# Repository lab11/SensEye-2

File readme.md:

# SensEye-2
**Sight-Guided Search and Depth Detection**

Based on the original SensEye design by Russ Bielawaski:  [repo](https://github.com/downbeat/senseye) 

##System Architecture

See the diagram below for an overview of the hardware and software stack for SensEye-2:

##OpenCV Image Processing
There are currently two python scripts written to implement OpenCV functions on top of images captured from the system. They are located in `software/client/opencv_detection` and also have the ability to measure run-time. Examples are shown below:
### Blob Detection 
Used to find the location of the pupil on the inward facing camera.

	python blob_detect.py
	Runtime of Blob Detection: 0.161993980408 seconds

### Depth Detection
Used to calculate the depth of the image based on the disparity between the two outward facing cameras.

	python disparity.py
	Runtime of Depth Detection: 0.360285043716 seconds

To complete this processing in real-time on the host computer, the run-time would have to be on the order of `0.04 seconds` as the imager captures images at a rate of approximately `25 hertz`.   

## Installation
### A note on operating systems
This installation uses Windows for Libero and Linux for uCLinux compilation. 
Specifically, 64-bit Windows 8 and 64-bit Ubuntu 14.04 LTS. Other options may be
successful

### Libero SoC
1. Download Libero from the following [link](http://www.microsemi.com/products/fpga-soc/design-resources/design-software/libero-soc#downloads).

2. Register for free gold 1-year disk ID locked license, follow instructions in email  

3. Install service pack update (if on Windows 8, you may need to disable driver signatures in order to install the FlashPro driver)

**Note**: Libero can be installed on Linux, but has been found to be problematic

### OpenCV
1. Download and install OpenCV, this [link](http://milq.github.io/install-opencv-ubuntu-debian/) worked well.
2. Ensure OpenCV installed in `/usr/local/include/`

### TFTP Server
1. Download and install a TFTP server, this [link](https://mohammadthalif.wordpress.com/2010/03/05/installing-and-testing-tftpd-in-ubuntudebian/) worked well.

## Setup

### Libero Project
1. Open `senseye.prjx` (you will get errors: "Unable to find..."")

2. Double click TOPLEVEL in the Design Hierarchy area to open it in the main window

3. Double click MSS\_CORE3\_MSS\_0 to open it in a new tab  
    1. Double click the ENVM block
    2. Right click the first client listed and select Modify Client.
    3. Change the location of the memory file to `your_SensEye-2_location\SensEye-2\software\smartfusion\Emcraft_Firmware\u-boot.hex`. 
    4. Click the Generate Component button in the main window (yellow cylinder with gear). 

4. Go to TOPLEVEL tab  
5. Click the Generate Programming Data button in the Design Flow area (green arrow)

Project should build appropriately.

**Note**: Ensure all of the MSS components are updated by clicking the Catalog tab then the `Download them now!` button (Libero should show the message `New cores are available`). Also ensure reset line into imager is inverted (in TOPLEVEL).

### uCLinux Build Environment
Open the Linux Cortex M User Manual available from Emcraft's SmartFusion webpage  
Follow the directions in Section 4.1

The `linux-cortexm-1.12.0/` folder should be extracted to the same location as the git repo  
(To get a new version of the cross-compiler, click [here](http://www.mentor.com/embedded-software/sourcery-tools/sourcery-codebench/editions/lite-edition/arm-uclinux.html), but you should probably stick with the one given by emcraft)  

`.bashrc` will need to be updated to run the following:

    cd <linux install directory>
    . ACTIVATE.sh
    cd -

**Note**: the cross compiler tools work for me on 64-bit fedora, but not in a shared folder. You may need to install ia32-libs or equivalent if you are on a 64-bit system

### TFTP Server
Test that the server is working by running:

    touch <tftpboot directory>/foo
    tftp 127.0.0.1
    get foo
    quit

**Note**: sometimes it is necessary to run this with `sudo`. 

The get request should complete immediately without an issue

Open a serial connection at 115200 baud. An example of this is below (assuming it is `ttyUSB0`)
	
	screen /dev/ttyUSB0 115200  

**Note**: Sometimes it is necessary to run this with `sudo` . Also if there is only a blank screen press `Enter` a few times and if that doesn't work, press `Ctrl-C` to kill the current program and reboot.

Find device IP address, from U-Boot:

    run flashboot
    udhcpc
    ifconfig
    reboot

Modify the environment variables on the SmartFusion board, from U-Boot:

    setenv netmask 255.255.255.0
    setenv gatewayip <device ip address top 24 bits>.1
    setenv ipaddr <device ip address>
    setenv serverip <server ip address>
    setenv image senseye_proj.uImage
    saveenv
    run netboot

### NFS Server
Follow instructions online to install an NFS server and enable it

After the device has booted run
    
    mount -t nfs -o proto=tcp,nolock,port=2049 <server ip address>:/<server nfs folder> /mnt

A script to do this has been included as `nfs.sh`

### Load Stonyman
Navigate to the `SensEye-2/software/uclinux/senseye_proj/` directory and edit `makescript`

	cp senseye_proj.uImage <your tftpboot directory>

Then run
    
    ./makescript

This should redirect all compile messages to the `compile.log` file. Run following commands on device

    ./load_stonyman.sh
    ./senseye_serv

The Stonyman controller software should now be loaded and ready to begin reading in images.

### Setting up client
Ensure OpenCV installed in `/usr/local/include/`

Change address of SmartFusion board in `SensEye-2/software/client/senseye_client/senseye_client.c` to current IP address (found by running `printenv` on the SmartFusion board):

    #define INSIGHT_SERV_ADDR     ("141.212.11.215") 

Navigate to the `SensEye-2/software/client/senseye_client` directory and run. 
  
    ./makescript

This should redirect all compile messages to the file `compile.out`

**Note**: while `senseye_serv` is running on the SmartFusion it waits for a connection from the client which is created by running `senseye_client`, then images should appear on the screen if a Stonyman is connected correctly.

### Hardware Configuration
The hardware can be somewhat tricky to configure correctly. First, build the circuit specified in `hardware/schematics/stonyman_breakout.pdf`. Ensure to tie a resistor (30k) to ground from the analog out (AN) of the Stonyman, and place a capacitor across the power supply rails.

**Calibration:** The configuration of the parameters in `software/uclinux/stonyman/stonyman_2.h` is dependent on whether the system is run at 3.3 Volts or 5 Volts. As of now the system is configured for 3.3 V. This can be changed by modifying the `define` statements based on empirical evidence.

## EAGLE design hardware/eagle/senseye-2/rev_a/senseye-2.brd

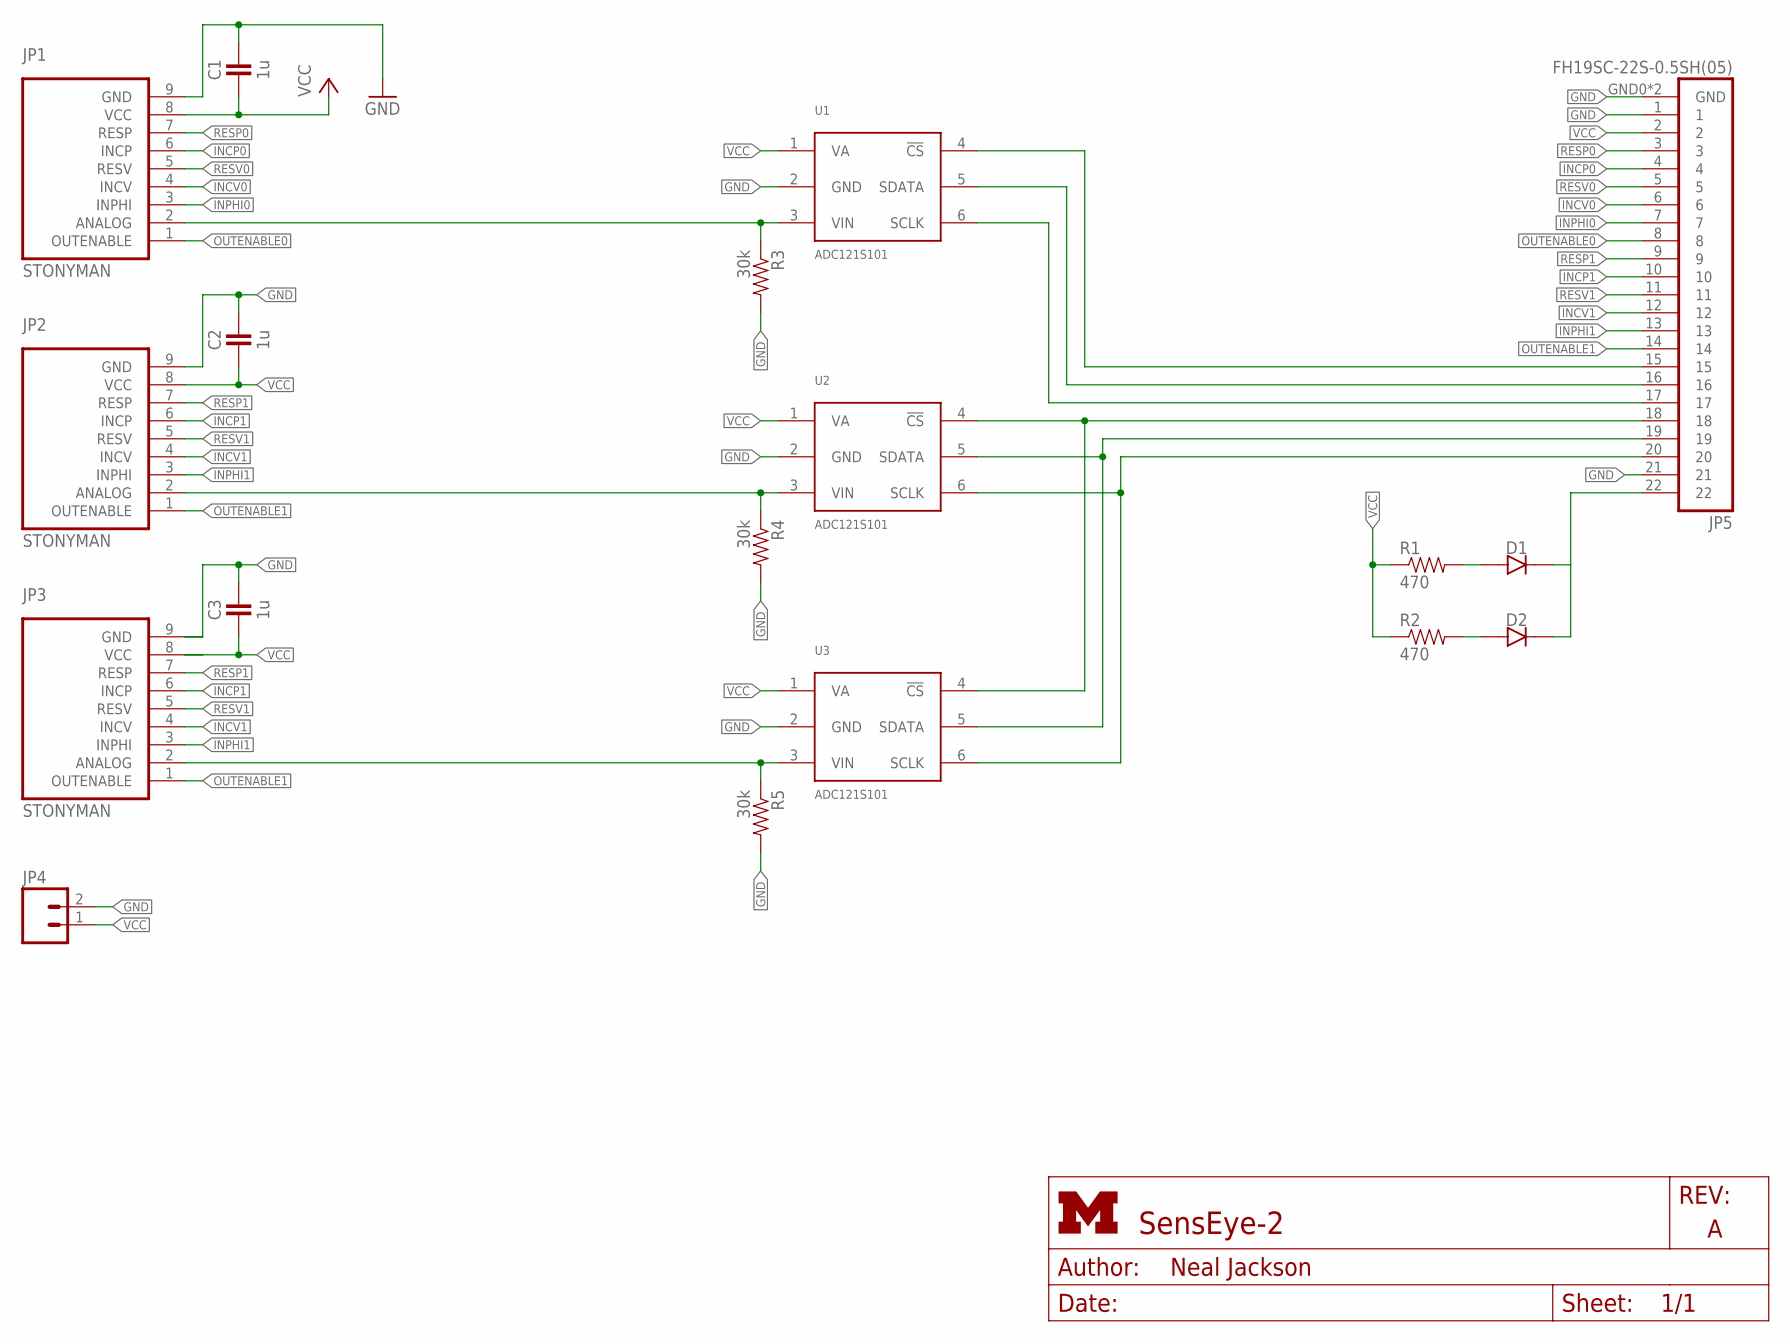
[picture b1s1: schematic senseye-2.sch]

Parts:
C1, C2, C3: 1u; 0402_CAP
D1, D2: DIODE0603; 0603-DIODE
JP1, JP2, JP3: STONYMAN; 1X09
JP4: M02PTH; 1X02
JP5: FH19SC-22S-0.5SH(05)
R1, R2: 470; 0402_RES
R3, R4, R5: 30k; 0402_RES
U1, U2, U3: ADC121S101; SOT-23-6

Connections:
!CS0: JP5.15, U1.4 (!CS)
ANALOG0: JP1.2 (ANALOG), R3.1, U1.3 (VIN)
GND: C1.1, C2.1, C3.1, JP1.9 (GND), JP2.9 (GND), JP3.9 (GND), JP4.2, JP5.1, JP5.21, JP5.GND0 (GND), JP5.GND1 (GND), R3.2, R4.2, R5.2, U1.2 (GND), U2.2 (GND), U3.2 (GND)
INCP0: JP1.6 (INCP), JP5.4
INCP1: JP2.6 (INCP), JP3.6 (INCP), JP5.10
INCV0: JP1.4 (INCV), JP5.6
INCV1: JP2.4 (INCV), JP3.4 (INCV), JP5.12
INPHI0: JP1.3 (INPHI), JP5.7
INPHI1: JP2.3 (INPHI), JP3.3 (INPHI), JP5.13
LED: D1.2 (CATHODE), D2.2 (CATHODE), JP5.22
unnamed: JP2.2 (ANALOG), R4.1, U2.3 (VIN)
unnamed: D1.1 (ANODE), R1.2
unnamed: JP3.2 (ANALOG), R5.1, U3.3 (VIN)
unnamed: D2.1 (ANODE), R2.2
unnamed: JP5.18, U2.4 (!CS), U3.4 (!CS)
OUTENABLE0: JP1.1 (OUTENABLE), JP5.8
OUTENABLE1: JP2.1 (OUTENABLE), JP3.1 (OUTENABLE), JP5.14
RESP0: JP1.7 (RESP), JP5.3
RESP1: JP2.7 (RESP), JP3.7 (RESP), JP5.9
RESV0: JP1.5 (RESV), JP5.5
RESV1: JP2.5 (RESV), JP3.5 (RESV), JP5.11
SCLK0: JP5.17, U1.6 (SCLK)
SCLK1: JP5.20, U2.6 (SCLK), U3.6 (SCLK)
SDATA0: JP5.16, U1.5 (SDATA)
SDATA1: JP5.19, U2.5 (SDATA), U3.5 (SDATA)
VCC: C1.2, C2.2, C3.2, JP1.8 (VCC), JP2.8 (VCC), JP3.8 (VCC), JP4.1, JP5.2, R1.1, R2.1, U1.1 (VA), U2.1 (VA), U3.1 (VA)

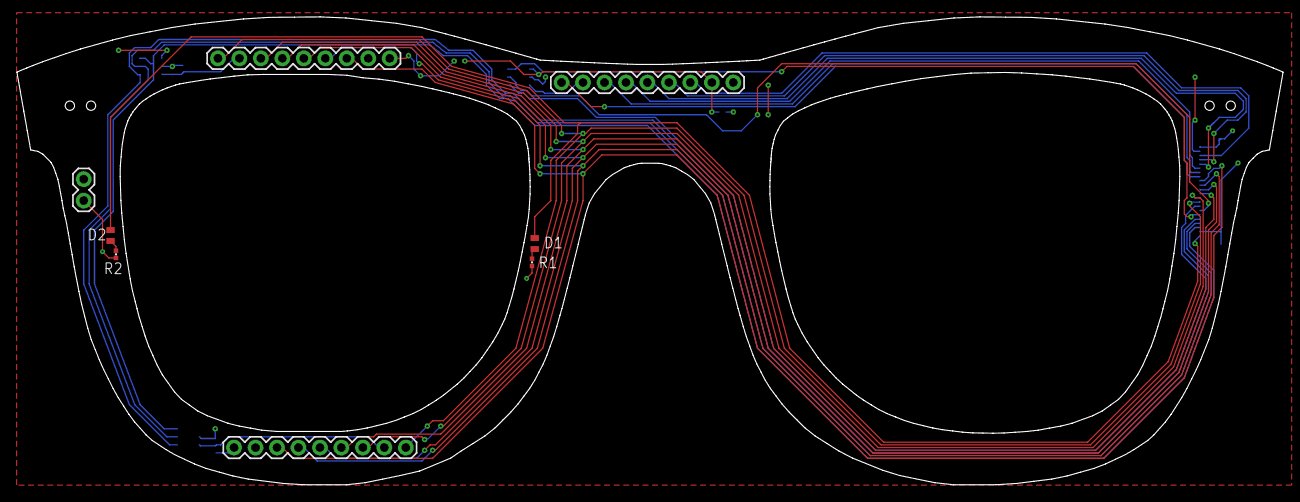
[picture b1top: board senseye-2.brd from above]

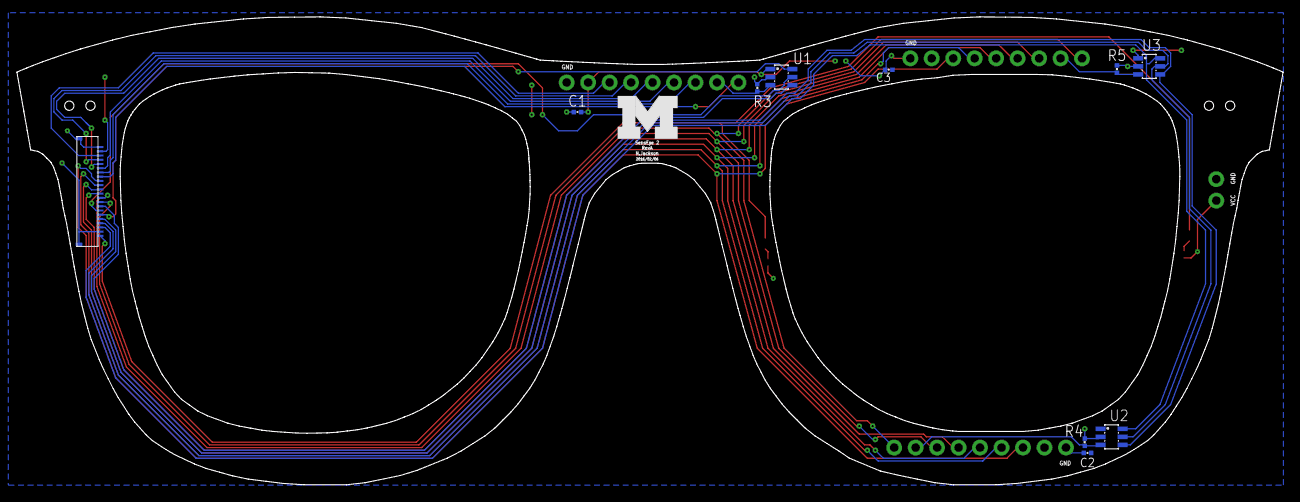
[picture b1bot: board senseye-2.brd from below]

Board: 2 copper layers, 149.8 x 55.3 mm, 19 parts (11 on the bottom side), 26 nets.

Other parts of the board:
U$1: UMICH_SOLID_200MIL

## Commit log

2014-01-17 Removed files that shouldn't be tracked
2014-01-19 Created new controller for the stonyman imager
    Needs a rework on the ADC controller, FIFO, and APB driver as well as a
    new frame mask controller before it can be used
2014-01-19 Created new controller for the ADC
2014-01-21 Created APB driver. Working on framemask and toplevel
2014-01-22 Finished APB interface. Connected modules at toplevel
2014-01-23 Created testbench for apb interface
2014-01-24 Added autogenerated FIFO file
2014-01-24 Register thine outputs
2014-01-24 Updates to interface for testing
2014-01-24 Testing new verilog backend
2014-01-24 Modified ADC Controller. Was missing an initial assignment for timer_nxt
2014-01-27 Modified apb interface to allow it to control timing parameters
    Also upgraded the fifo to hold more data
2014-01-27 dos2unix on everything windows touched
2014-01-27 Modified permissions of uclinux directory
    Create makescript to create uImage and move to ~/tftpboot
2014-01-28 Added new busy signal to the stonyman controller
2014-02-02 Revamped smartfusion folder
    Removed junk that had accumulated
    Updated to Libero 11.2 sp1
    Moved new HDL files
2014-02-02 Added gitignore to avoid committing Actel folder which is large and unneccessary
2014-02-04 Updates to hdl files
2014-02-04 Updates from mac
    NFS mounting script
    Smartfusion reference guide
    Start of new kernel driver
2014-02-04 Created readme file for project
    Also project management such as:
    New .gitignores!!
    Scripts folder!!
    Installation instructions!! (in readme)
2014-02-10 Kernel driver upgrades
    Kernel can now run up to 67 Hz (if the server could handle that)
    Frame masks are not yet implemented
2014-02-10 Fixed windows line endings sublime had stupidly added
2014-02-10 Modified hdl to work at 5v
2014-03-03 Updated verilog to run two cameras simultaneously
    Also attempting to add ability to modify pixel offset values, currently
    not succeeding. Possibly due to size constraints?
2014-03-03 Updated client to handle 2 cameras simultaneously
    Also created senseye_client which is a combination of the websocket and
    the display
2014-03-03 Updated server-side files to handle 2 cameras
    Also changed them to work with senseye_client
2014-03-04 Got image masks working again
    Images correct to an average value found by covering imager
    Pressing 'm' in the client window will save new mask files
2014-03-04 Reduced gates used from 96% to 56%
    Finished implementing kernel-defined ADC offset
2015-02-23 added wiring schematic for stonyman breakout board
2015-03-18 Updated Libero design to include updated verilog files
2015-03-19 updated readme with Libero instructions
2015-03-19 load stonyman section updated
2015-03-19 client working, updated readme
2015-03-19 updated readme to include changing IP
2015-03-19 updated readme to change location of boot file
2015-03-19 organized readme
2015-03-19 Add attribution for Russ
2015-03-19 Spacing fix
2015-03-19 Spacing fix #2
2015-03-25 edited readme
2015-03-30 modified senseye_serv_2.c to not send second cam
2015-04-10 updated schematic
2015-04-29 turned off framemask
2015-04-29 readme grammar
2015-04-29 updated tagline
2015-11-13 updated to work on 3.3 V stonyman
2015-11-13 updated readme with hardware configuration
2015-11-30 updated uclinux config settings
2015-12-03 updated readme with system diagrams
2015-12-07 calibrated to 3.3 V
2015-12-07 working right mask for 3.3 V
2015-12-14 working with 2 cameras
2016-01-15 opencv blob and depth detection working
2016-01-20 updated readme and opencv
2016-01-20 added opencv results
2016-02-05 layout of glasses finished
2016-02-05 added power header
2016-02-05 start temples of glasses
2016-02-07 using spi instead of i2c
2016-02-08 first version pupil_detect.v
2016-02-08 updated verilog
2016-02-08 added drills for hinges
2016-02-08 routed and marked holes
2016-02-08 clean up gnd route around drill holes
2016-02-08 rename to right temple
2016-02-09 empty left temple
2016-02-09 added inline resistors for diodes
2016-02-09 moved labels
2016-02-09 moved all to 0,0 origin
2016-02-09 gerbmerge config
2016-02-09 uncommented
2016-02-09 adding temp gerb files
2016-02-09 use oln instead of mil
2016-02-09 remove gerber files, changed silkscreen layer for name and date
2016-02-09 rev_a documentation and fab
2016-02-15 Restored datasheets directory
    Moved eagle files to hardware/eagle/
2016-02-17 pupil detect compiles
2016-03-11 updated eagle with 30k resistor
2016-03-25 adc_controller working in sim
2016-03-25 updated stonyman_controller working in sim
2016-04-04 pupil detect working in sim
2016-04-08 updated senseye_client to ip addr as input
2016-04-13 cam working with pupil detect
2016-04-22 refined pupil-detect simulation and threshold

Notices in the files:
parts and their libraries:
SparkFun-Connectors: Licensing: CC v3.0 Share-Alike You are welcome to use this library for commercial purposes.
